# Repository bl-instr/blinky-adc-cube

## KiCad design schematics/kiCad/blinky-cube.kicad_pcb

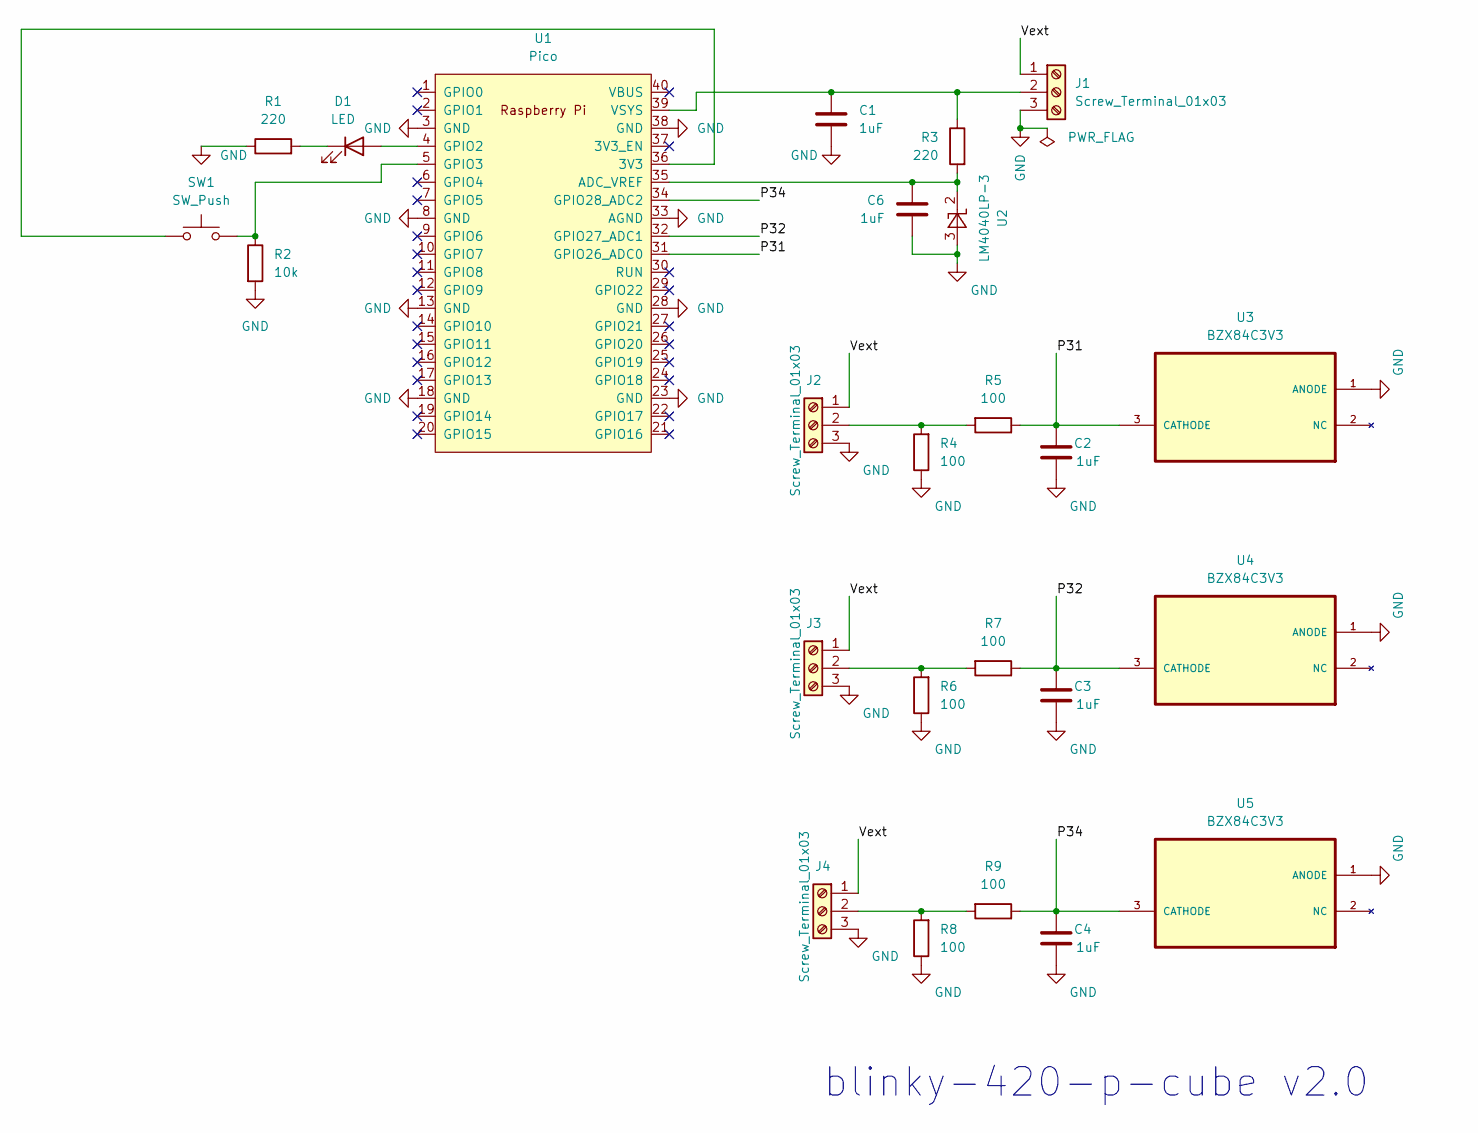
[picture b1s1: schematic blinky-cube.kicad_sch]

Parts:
C1, C2, C3, C4, C6: 1uF; C_1206_3216Metric_Pad1.33x1.80mm_HandSolder
D1: LED; LED_D5.0mm
J1, J2, J3, J4: Screw_Terminal_01x03; TerminalBlock_bornier-3_P5.08mm
R1, R3: 220; R_1206_3216Metric_Pad1.30x1.75mm_HandSolder
R2: 10k; R_1206_3216Metric_Pad1.30x1.75mm_HandSolder
R4, R5, R6, R7, R8, R9: 100; R_1206_3216Metric_Pad1.30x1.75mm_HandSolder
SW1: SW_Push; SW_PUSH_6mm
U1: Pico; RPi_Pico_SMD_TH
U2: LM4040LP-3; TO-92_Inline
U3, U4, U5: BZX84C3V3; SOT91P240X110-3N; MPN BZX84C3V3

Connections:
/P31: C2.1, R5.1, U1.31 (GPIO26_ADC0), U3.3 (CATHODE)
/P32: C3.1, R7.1, U1.32 (GPIO27_ADC1), U4.3 (CATHODE)
/P34: C4.1, R9.1, U1.34 (GPIO28_ADC2), U5.3 (CATHODE)
/Vext: J1.1, J2.1, J3.1, J4.1
GND: C1.2, C2.2, C3.2, C4.2, C6.2, J1.3, J2.3, J3.3, J4.3, R1.1, R2.2, R4.1, R6.1, R8.1, U1.3 (GND), U1.8 (GND), U1.13 (GND), U1.18 (GND), U1.23 (GND), U1.28 (GND), U1.33 (AGND), U1.38 (GND), U2.3 (A), U3.1 (ANODE), U4.1 (ANODE), U5.1 (ANODE)
unnamed: D1.2 (A), U1.4 (GPIO2)
unnamed: D1.1 (K), R1.2
unnamed: C1.1, J1.2, R3.1, U1.39 (VSYS)
unnamed: J2.2, R4.2, R5.2
unnamed: J3.2, R6.2, R7.2
unnamed: J4.2, R8.2, R9.2
unnamed: SW1.1, U1.36 (3V3)
unnamed: C6.1, R3.2, U1.35 (ADC_VREF), U2.2 (K)
unnamed: R2.1, SW1.2, U1.5 (GPIO3)

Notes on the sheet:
blinky-420-p-cube v2.0

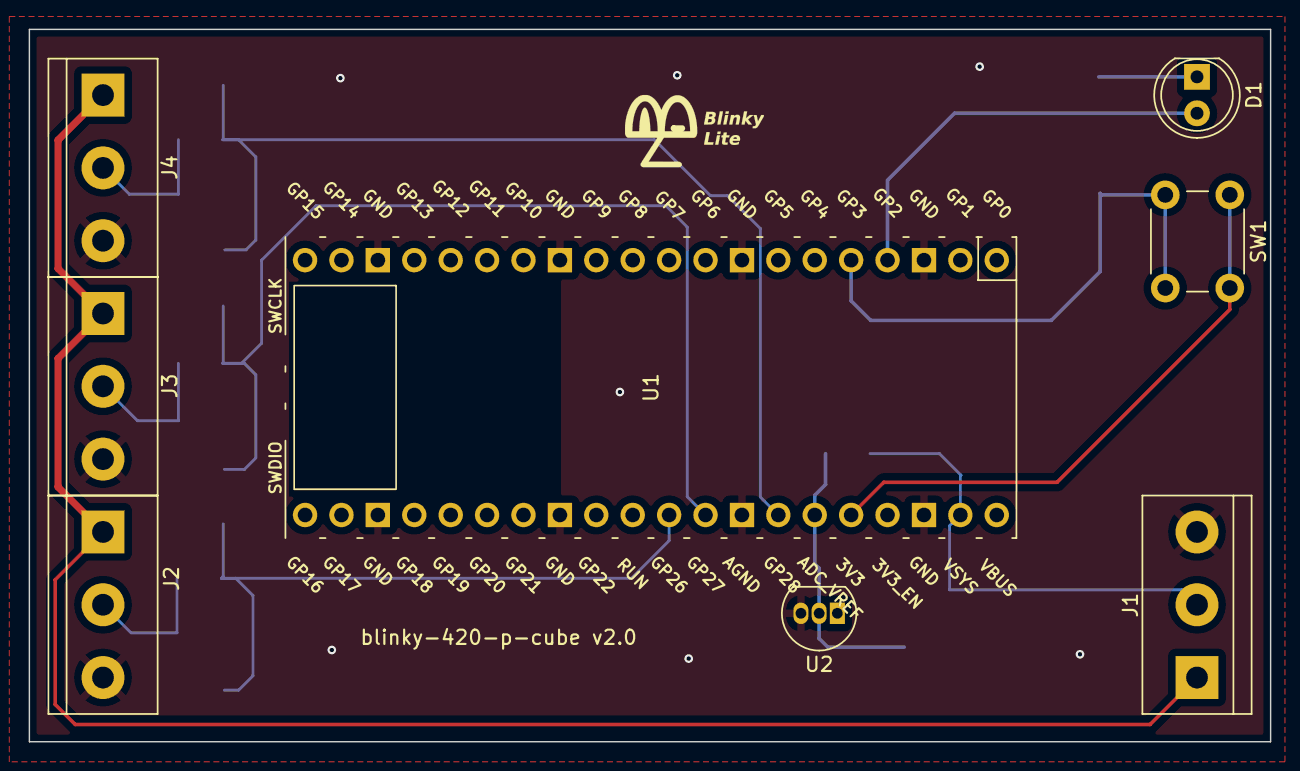
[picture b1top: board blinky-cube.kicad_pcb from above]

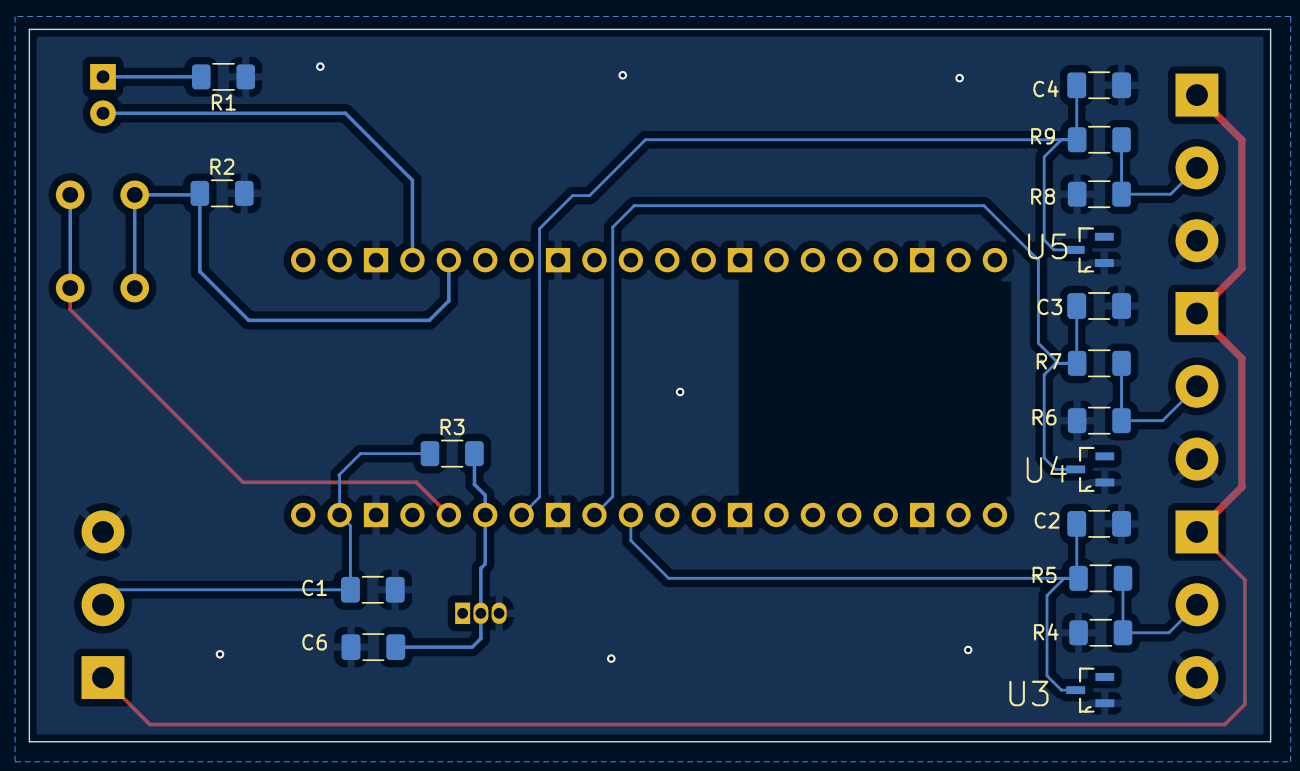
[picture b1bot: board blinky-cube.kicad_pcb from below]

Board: 2 copper layers, 86.6 x 49.7 mm, 25 parts (17 on the bottom side), 14 nets.

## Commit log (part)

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2024-02-22 added bom
2024-03-10 working with contorl system
2024-03-19 switched to one core
2024-09-26 first commit of prototype
2025-01-27 new platform
